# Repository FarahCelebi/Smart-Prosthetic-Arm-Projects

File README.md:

## Smart Prosthetic Arm

A six-project open hardware and firmware system for a surface EMG-controlled
prosthetic arm. The system reads muscle electrical signals from surface
electrodes, classifies hand gestures in real time, and drives a
servo-actuated prosthetic hand accordingly. Each project is a self-contained,
fully documented deliverable — schematic, PCB layout, Gerbers, and README —
designed to be fabricated and tested independently before integration.

## System Architecture

```
Surface electrodes
       │
       ▼
┌─────────────────┐
│  Project 1      │  EMG Acquisition Board
│  EMG signals    │  Dual-channel INA333 + ADS1115
│  → I²C out      │  Gain ~404×, 16-bit ADC
└────────┬────────┘
         │ I²C
         ▼
┌─────────────────┐
│  Project 2      │  Gesture Classifier Firmware
│  STM32 firmware │  Real-time EMG feature extraction
│  → gesture ID   │  + ML-based gesture classification
└────────┬────────┘
         │ I²C / UART
         ▼
┌─────────────────┐     ┌─────────────────┐
│  Project 3      │     │  Project 4      │
│  Servo Driver   │     │  BLE Module     │
│  PCA9685 PWM    │     │  nRF52840       │
│  6× servo out   │     │  Wireless telem │
└────────┬────────┘     └─────────────────┘
         │
         ▼
┌─────────────────┐
│  Project 5      │  IMU + EMG Sensor Fusion
│  ICM-42688-P    │  Accelerometer + gyroscope
│  + sensor fusion│  fused with EMG for robustness
└────────┬────────┘
         │
         ▼
┌─────────────────┐
│  Project 6      │  Full Integration Capstone
│  All subsystems │  Complete assembled arm system
│  integrated     │  End-to-end validation
└─────────────────┘
```

## Projects

| # | Project | Type | Description |
|---|---|---|---|
| 01 | [EMG Acquisition Board](./Project-1-EMG-Acquisition) | PCB | Dual-channel surface EMG acquisition board using INA333 instrumentation amplifiers and an ADS1115 16-bit ADC. Conditions raw muscle signals through a 404× gain chain with high-pass filtering and anti-alias filtering before I²C output. |
| 02 | [Gesture Classifier Firmware](./Project-2-Gesture-Classifier) | Firmware | Real-time gesture classification firmware running on the STM32F411, fusing dual-channel EMG features with ICM-42688-P IMU data to classify six hand gestures. Outputs servo position commands over I²C and streams telemetry to the BLE module over UART. |
| 03 | [Servo Driver Board](./Project-3-Servo-Driver) | PCB | PCA9685-based 16-channel PWM controller driving six servo motors for prosthetic hand finger and wrist actuation over I²C. Separate 5–6V servo power rail with 2000µF bulk capacitance isolates motor switching transients from the logic supply. |
| 04 | [BLE Telemetry Module](./Project-4-BLE-Telemetry-Module) | PCB | Bare nRF52840-QIAA BLE 5.0 transceiver board with full RF front-end design including pi-network antenna matching and quarter-wave wire antenna. Accepts USB or LiPo power through a dual-input OR-ing diode circuit with a low-dropout XC6210 LDO. |
| 05 | [IMU + EMG Sensor Fusion](./Project-5-IMU+EMG-Sensor-Fusion) | PCB | ICM-42688-P 6-axis IMU board providing wrist orientation and motion data over high-speed SPI to complement EMG signals in the gesture classifier. Includes an I²C passthrough header matching the EMG board pinout for minimal wiring harness on the arm. |
| 06 | [Full Integration Capstone](./Project-6-Full-Integration-Capstone) | PCB + Firmware | Central hub board hosting the STM32F411 main MCU and routing power, I²C, SPI, and UART signals between all five subsystem boards through pinout-matched connectors. Runs the gesture classifier firmware and coordinates the complete prosthetic arm system from a single 3.7V LiPo cell. |

## Hardware Stack

| Component | Role |
|---|---|
| INA333 (×2) | Instrumentation amplifier |
| ADS1115 | 16-bit I²C ADC |
| TLV2372 | Second-stage op-amp |
| PCA9685PW | 16-channel PWM servo controller |
| nRF52840 | BLE 5.0 + ARM Cortex-M4 |
| ICM-42688-P | 6-axis IMU (accelerometer + gyroscope) |

## Tools

- KiCad (PCB design)
- GitHub Desktop (version control)
- Zephyr RTOS / STM32 HAL (firmware)

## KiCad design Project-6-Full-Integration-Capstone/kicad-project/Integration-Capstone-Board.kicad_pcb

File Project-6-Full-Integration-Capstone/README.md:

# Integration-Capstone-Board

The central hub of the Smart Prosthetic Arm system, designed as Project 6
of 6. This board hosts the main STM32F411RETx microcontroller and provides
the physical connectors, power distribution, and signal routing that ties
all five subsystem boards into a unified wearable system — the EMG
Acquisition Board, Servo Driver Board, BLE Module, IMU Sensor Fusion Board,
and the Gesture Classifier firmware running on the STM32 itself.

## Schematic

## PCB Layout

## 3D View

## Overview

Rather than designing another standalone sensor or actuator board, the
capstone solves the real system integration challenge — making five
independent boards work together reliably as a wearable prosthetic arm.
The STM32F411 reads dual-channel EMG data from the ADS1115 over I²C,
reads 6-axis IMU data from the ICM-42688-P over SPI, classifies the
fused sensor data into one of six hand gestures, sends servo position
commands to the PCA9685 over I²C, and streams telemetry to the nRF52840
BLE module over UART — all concurrently, from a single board running on
a 3.7V LiPo battery.

## System Connections

| Connector | Subsystem | Interface | Pinout match |
|---|---|---|---|
| J4 | EMG Acquisition Board | I²C1 | Matches EMG board J3 |
| J5 | IMU Sensor Fusion Board | SPI1 + INT1 | Matches IMU board J2 |
| J6 | IMU I²C Passthrough | I²C2 | Matches IMU board J3 |
| J7 | BLE Module | UART1 + SPI1 + I²C1 + SWD | Matches BLE board J3 |
| J8 | Servo Driver Board | I²C1 | Matches servo driver J9 |
| J9 | USB | Programming + CDC | Micro-B |

All connector pinouts were designed from the start of the project to match
across boards — plugging any subsystem board into its corresponding header
requires no adapter and no rewiring.

## Design Notes

**Dual I²C bus architecture:** The STM32F411 has two I²C peripherals. I²C1
(PB6/PB7) is the main system bus, shared between the EMG Acquisition Board
(ADS1115, address 0x48), the Servo Driver Board (PCA9685, address 0x40),
and the BLE module's I²C lines. I²C2 (PB10/PB11) is a dedicated bus for
the IMU board's I²C passthrough header — isolating the IMU's local I²C
traffic from the main system bus prevents address conflicts and reduces bus
loading. Separate 10kΩ pull-up pairs (R3/R4 for I²C1, R5/R6 for I²C2)
are placed immediately beside their respective connectors.

**SPI bus sharing:** SPI1 (PA5/PA6/PA7) is shared between the IMU Sensor
Fusion Board (J5) and the BLE module (J7). The IMU chip select (IMU_CS on
PA4) and the BLE module's SPI CS are managed independently by the firmware,
allowing both devices on the same SPI bus without conflict. SPI was chosen
for the IMU over I²C to allow data rates up to 24MHz — necessary for high
ODR IMU sampling concurrent with BLE activity.

**Power architecture:** A single LiPo cell (3.7V nominal) connects to J1.
The AMS1117-3.3 LDO (U1) regulates this to 3.3V for the STM32, crystal,
and all subsystem connector power pins. A 100µF bulk electrolytic capacitor
(C5) is placed immediately at J1 to handle inrush current during system
startup when all five subsystem boards power up simultaneously. J2 is a
separate screw terminal for the 6V servo power rail — this passes directly
to the Servo Driver Board via cable and is never routed across the
integration board's PCB, keeping high-current servo switching noise isolated
from the logic rail.

**Crystal and USB:** A 25MHz crystal (Y1) provides the STM32's PLL
reference for accurate USB CDC operation. Load capacitors C6 and C7 (12pF
each) are placed immediately beside PH0 and PH1 with no vias on the
oscillator traces. USB D+ and D− pass through the USBLC6-2SC6 ESD
protection device (U3) placed immediately adjacent to J9, then through 22Ω
series resistors before reaching PA11 and PA12. The USB VBUS pin connects
to the VBAT net — when USB is connected it powers the board directly,
supplementing or replacing the LiPo without additional power management
circuitry.

**Reset and boot:** SW1 is a tactile push button connected to NRST with a
10kΩ pull-up to +3.3V, placed close to U2's NRST pin to minimise the reset
trace length. R2 pulls BOOT0 low by default for normal flash execution mode.
J3 is a 2-pin BOOT0 header that allows the STM32 to be put into DFU mode
by bridging pin 1 to +3.3V — used for initial firmware flashing before the
USB CDC interface is operational.

**Status LEDs:** Three LEDs provide system state visibility. D1 (green,
always on) connects directly from +3.3V through R9 — it illuminates
whenever the board is powered, requiring no firmware. D2 (blue) is driven
by PA3 through R10 and is toggled by firmware to indicate an active BLE
connection. D3 (yellow) is driven by PB0 through R11 and pulses on each
recognised gesture event. All three resistors are 330Ω giving approximately
8mA LED current at 3.3V supply — visible in indoor and outdoor conditions
without excessive current draw from the battery.

**Stackup rationale:** F.Cu carries all signal and power traces with no
copper pour. B.Cu carries a solid unbroken GND plane across the entire
board. This gives every signal trace — including the dense I²C, SPI, and
UART routing between U2 and the subsystem connectors — a direct return path
immediately beneath it, minimising crosstalk between the parallel bus
signals. A minimum of 4 vias are placed through the STM32's exposed GND pad
to the B.Cu plane for both electrical and thermal connection. Stitching vias
connect the board edge GND connections to the B.Cu plane around the
perimeter.

## GPIO Map

| GPIO | Function | Destination |
|---|---|---|
| PA3 | LED_BLE | D2 blue LED |
| PA4 | IMU_CS | J5 pin 6 |
| PA5 | SPI1_CLK | J5 pin 5, J7 pin 7 |
| PA6 | SPI1_MISO | J5 pin 4, J7 pin 6 |
| PA7 | SPI1_MOSI | J5 pin 3, J7 pin 5 |
| PA9 | UART1_TX | J7 pin 3 |
| PA10 | UART1_RX | J7 pin 4 |
| PA11 | USB_DM | J9 D− |
| PA12 | USB_DP | J9 D+ |
| PB0 | LED_GESTURE | D3 yellow LED |
| PB6 | I2C1_SCL | J4 pin 3, J7 pin 9, J8 pin 3 |
| PB7 | I2C1_SDA | J4 pin 4, J7 pin 8, J8 pin 4 |
| PB8 | IMU_INT1 | J5 pin 7 |
| PB9 | I2C2_SDA | J6 pin 4 |
| PB10 | I2C2_SCL | J6 pin 3 |
| PH0 | OSC_IN | Y1 pin 1 |
| PH1 | OSC_OUT | Y1 pin 2 |

## Manufacturing

- 2-layer stackup: F.Cu (signal + power) / B.Cu (solid GND plane)
- 1.6mm FR4, standard 1oz copper
- Passed DRC with 0 violations, 0 unconnected nets
- Gerbers and drill files generated

## Part of

Smart Prosthetic Arm — Project 6 of 6

## Tools

- KiCad

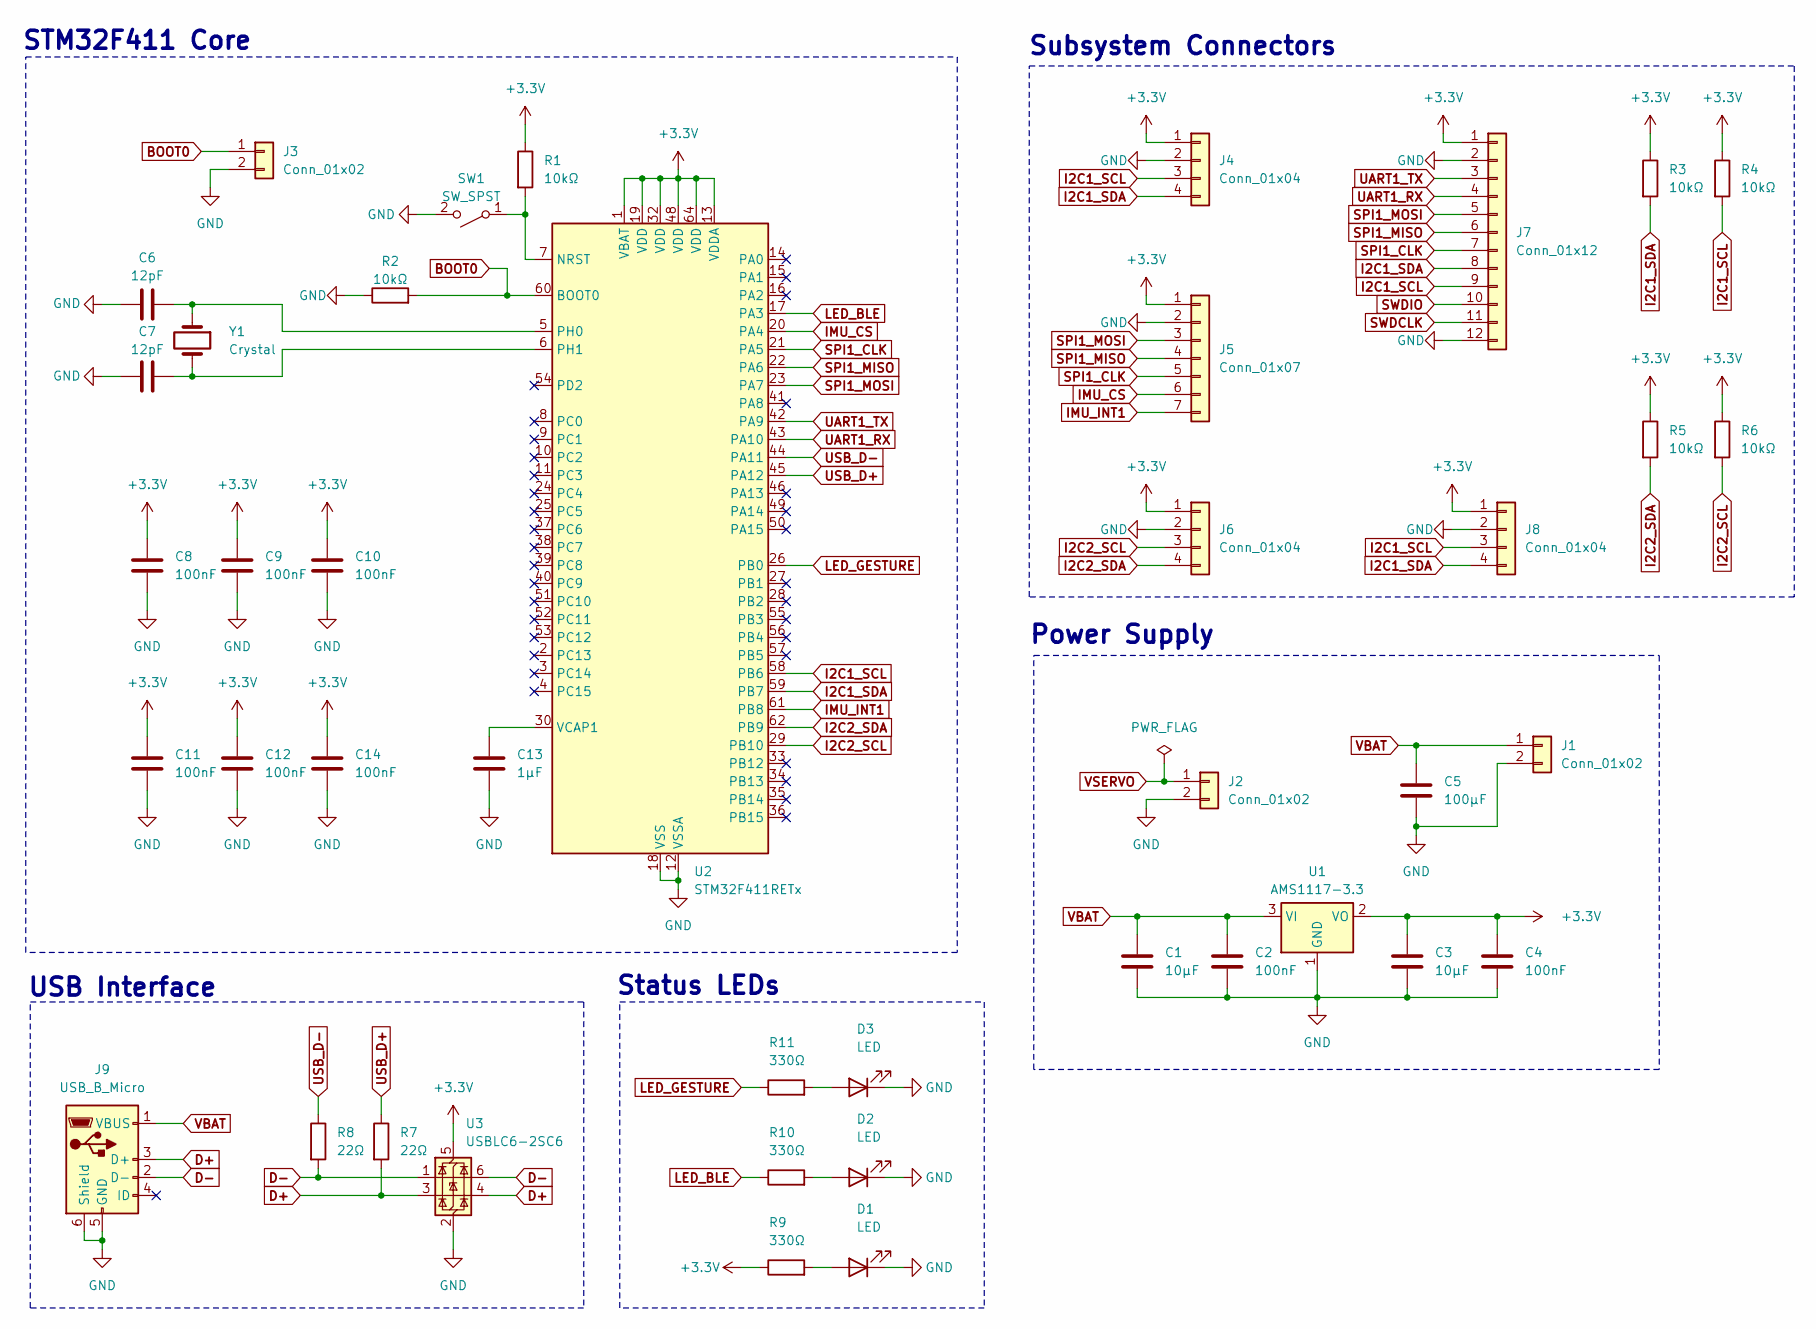
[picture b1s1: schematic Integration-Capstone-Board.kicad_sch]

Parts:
C1, C3: 10µF; C_0805_2012Metric
C2, C4, C8, C9, C10, C11, C12, C14: 100nF; C_0402_1005Metric
C5: 100µF; C_Radial_D8.0mm_H11.5mm_P3.50mm
C6, C7: 12pF; C_0402_1005Metric
C13: 1µF; C_0402_1005Metric
D1, D2, D3: LED; LED_0402_1005Metric
J1, J2: Conn_01x02; TerminalBlock_TE_282834-2_1x02_P2.54mm_Horizontal
J3: Conn_01x02; PinHeader_1x02_P2.54mm_Vertical
J4, J6, J8: Conn_01x04; PinHeader_1x04_P2.54mm_Vertical
J5: Conn_01x07; PinHeader_1x07_P2.54mm_Vertical
J7: Conn_01x12; PinHeader_1x12_P2.54mm_Vertical
J9: USB_B_Micro; USB_Micro-B_Amphenol_10118194_Horizontal
R1, R2, R3, R4, R5, R6: 10kΩ; R_0402_1005Metric
R7, R8: 22Ω; R_0402_1005Metric
R9, R10, R11: 330Ω; R_0402_1005Metric
SW1: SW_SPST; SW_SPST_PTS645Sx43SMTR92
U1: AMS1117-3.3; SOT-223-3_TabPin2
U2: STM32F411RETx; LQFP-64_10x10mm_P0.5mm
U3: USBLC6-2SC6; SOT-23-6
Y1: Crystal; Crystal_SMD_2520-4Pin_2.5x2.0mm

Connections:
+3.3V: C3.1, C4.1, C8.1, C9.1, C10.1, C11.1, C12.1, C14.1, J4.1, J5.1, J6.1, J7.1, J8.1, R1.1, R3.1, R4.1, R5.1, R6.1, R9.1, U1.2 (VO), U2.1 (VBAT), U2.13 (VDDA), U2.19 (VDD), U2.32 (VDD), U2.48 (VDD), U2.64 (VDD), U3.5 (VBUS)
BOOT0: J3.1, R2.2, U2.60 (BOOT0)
D+: J9.3 (D+), R7.2, U3.3 (I/O2), U3.4 (I/O2)
D-: J9.2 (D-), R8.2, U3.1 (I/O1), U3.6 (I/O1)
GND: C1.2, C2.2, C3.2, C4.2, C5.2, C6.1, C7.1, C8.2, C9.2, C10.2, C11.2, C12.2, C13.2, C14.2, D1.1 (K), D2.1 (K), D3.1 (K), J1.2, J2.2, J3.2, J4.2, J5.2, J6.2, J7.2, J7.12, J8.2, J9.5 (GND), J9.6 (Shield), R2.1, SW1.2 (B), U1.1 (GND), U2.12 (VSSA), U2.18 (VSS), U2.31 (VSS), U2.47 (VSS), U2.63 (VSS), U3.2 (GND), Y1.3, Y1.4
I2C1_SCL: J4.3, J7.9, J8.3, R4.2, U2.58 (PB6)
I2C1_SDA: J4.4, J7.8, J8.4, R3.2, U2.59 (PB7)
I2C2_SCL: J6.3, R6.2, U2.29 (PB10)
I2C2_SDA: J6.4, R5.2, U2.62 (PB9)
IMU_CS: J5.6, U2.20 (PA4)
IMU_INT1: J5.7, U2.61 (PB8)
LED_BLE: R10.1, U2.17 (PA3)
LED_GESTURE: R11.1, U2.26 (PB0)
unnamed: D1.2 (A), R9.2
unnamed: D2.2 (A), R10.2
unnamed: D3.2 (A), R11.2
unnamed: R1.2, SW1.1 (A), U2.7 (NRST)
unnamed: C6.2, U2.5 (PH0), Y1.1
unnamed: C7.2, U2.6 (PH1), Y1.2
unnamed: C13.1, U2.30 (VCAP1)
SPI1_CLK: J5.5, J7.7, U2.21 (PA5)
SPI1_MISO: J5.4, J7.6, U2.22 (PA6)
SPI1_MOSI: J5.3, J7.5, U2.23 (PA7)
SWDCLK: J7.11
SWDIO: J7.10
UART1_RX: J7.4, U2.43 (PA10)
UART1_TX: J7.3, U2.42 (PA9)
USB_D+: R7.1, U2.45 (PA12)
USB_D-: R8.1, U2.44 (PA11)
VBAT: C1.1, C2.1, C5.1, J1.1, J9.1 (VBUS), U1.3 (VI)
VSERVO: J2.1

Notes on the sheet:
STM32F411 Core
Status LEDs
Subsystem Connectors
Power Supply
USB Interface

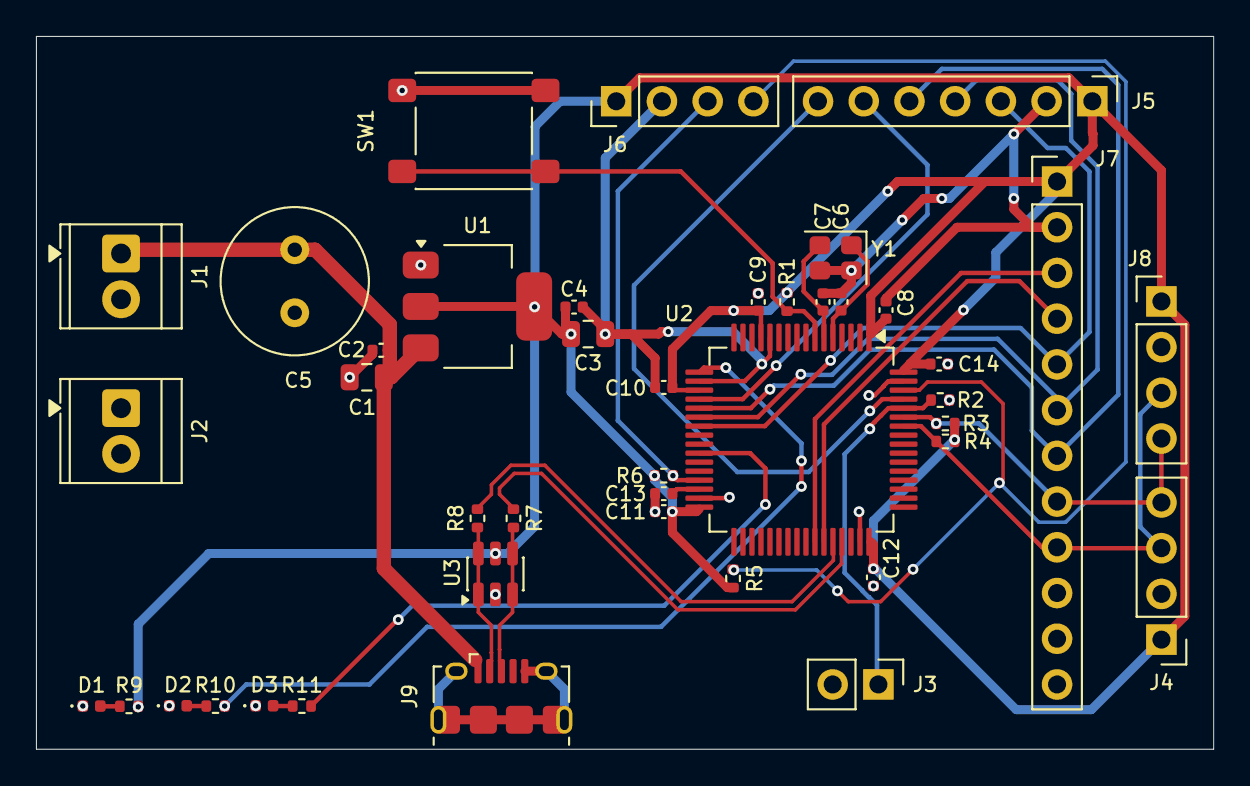
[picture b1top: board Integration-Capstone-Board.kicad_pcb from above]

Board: 2 copper layers, 65.4 x 39.6 mm, 42 parts (0 on the bottom side), 28 nets.

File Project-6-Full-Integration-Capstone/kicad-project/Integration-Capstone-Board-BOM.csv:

"Id";"Designator";"Footprint";"Quantity";"Designation";"Supplier and ref";
1;"J6,J8,J4";"PinHeader_1x04_P2.54mm_Vertical";3;"Conn_01x04";;;
2;"C3,C1";"C_0805_2012Metric";2;"10µF";;;
3;"R4,R3,R1,R5,R6,R2";"R_0402_1005Metric";6;"10kΩ";;;
4;"C5";"C_Radial_D8.0mm_H11.5mm_P3.50mm";1;"100µF";;;
5;"R10,R11,R9";"R_0402_1005Metric";3;"330Ω";;;
6;"D3,D2,D1";"LED_0402_1005Metric";3;"LED";;;
7;"U3";"SOT-23-6";1;"USBLC6-2SC6";;;
8;"C10,C12,C14,C8,C11,C4,C9,C2";"C_0402_1005Metric";8;"100nF";;;
9;"C6,C7";"C_0402_1005Metric";2;"12pF";;;
10;"C13";"C_0402_1005Metric";1;"1µF";;;
11;"U2";"LQFP-64_10x10mm_P0.5mm";1;"STM32F411RETx";;;
12;"R7,R8";"R_0402_1005Metric";2;"22Ω";;;
13;"J2,J1";"TerminalBlock_TE_282834-2_1x02_P2.54mm_Horizontal";2;"Conn_01x02";;;
14;"J3";"PinHeader_1x02_P2.54mm_Vertical";1;"Conn_01x02";;;
15;"U1";"SOT-223-3_TabPin2";1;"AMS1117-3.3";;;
16;"J7";"PinHeader_1x12_P2.54mm_Vertical";1;"Conn_01x12";;;
17;"Y1";"Crystal_SMD_2520-4Pin_2.5x2.0mm";1;"Crystal";;;
18;"J9";"USB_Micro-B_Amphenol_10118194_Horizontal";1;"USB_B_Micro";;;
19;"SW1";"SW_SPST_PTS645Sx43SMTR92";1;"SW_SPST";;;
20;"J5";"PinHeader_1x07_P2.54mm_Vertical";1;"Conn_01x07";;;

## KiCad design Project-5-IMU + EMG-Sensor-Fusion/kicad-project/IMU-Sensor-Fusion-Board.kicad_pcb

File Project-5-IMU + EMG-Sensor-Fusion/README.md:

# IMU-Sensor-Fusion-Board

A TDK InvenSense ICM-42688-P based 6-axis IMU board designed as Project 5
of the Smart Prosthetic Arm system. The board adds wrist orientation and
motion context to the dual-channel EMG signals from the EMG Acquisition
Board, enabling the gesture classifier firmware to distinguish between
gestures that produce similar EMG patterns but differ in wrist orientation —
significantly improving real-world classification accuracy.

## Schematic

## PCB Layout

## 3D View

## Overview

The ICM-42688-P integrates a 3-axis gyroscope and 3-axis accelerometer in a
compact 2.5×3.0mm LGA-14 package, providing full 6-axis motion data over a
high-speed SPI interface at up to 24MHz. The board exposes the SPI bus,
chip select, and both interrupt lines through a 7-pin header for direct
connection to the host microcontroller, and passes through the I²C bus on a
4-pin header matching the EMG Acquisition Board pinout — allowing the host
to communicate with the ADS1115 ADC and the IMU simultaneously without
additional wiring.

## Design Notes

**IMU selection:** The ICM-42688-P was selected over lower-tier IMUs such as
the MPU6050 for several reasons directly relevant to prosthetic arm use. Its
gyroscope noise density of 2.8 mdps/√Hz and accelerometer noise density of
65 µg/√Hz are among the lowest available in a single-package 6-axis device,
enabling detection of subtle wrist rotation and fine finger-positioning
gestures that would be buried in noise on a less capable sensor. The device
also supports output data rates up to 32kHz, providing substantial
oversampling headroom for the sensor fusion algorithm. The 1.71–3.6V supply
range is directly compatible with the 3.3V system rail without a dedicated
LDO.

**SPI interface:** The ICM-42688-P is operated in 4-wire SPI mode. AP_CS
(pin 12) is the chip select, held high by R1 (10kΩ pull-up to +3.3V) when
the bus is idle. AP_SCL/AP_SCLK (pin 13) is the clock, AP_SDA/AP_SDI
(pin 14) is MOSI, and AP_SDO/AP_AD0 (pin 1) is MISO. In SPI mode the
AP_AD0 function of pin 1 is overridden by the chip select state at power-up
— AP_CS tied high ensures SPI mode is selected correctly.

**Reserved pin handling:** The ICM-42688-P datasheet specifies explicit
requirements for each reserved pin. RESV_7 (pin 7) must be connected to GND
— this is mandatory and not optional. RESV_2 (pin 2) and RESV_3 (pin 3) may
be left unconnected or tied to GND — both are tied to GND on this board for
noise immunity. RESV_10 (pin 10) and RESV_11 (pin 11) may be left
unconnected — no-connect flags are placed on both.

**FSYNC/CLKIN pin (pin 9):** The INT2/FSYNC/CLKIN pin serves three functions
depending on firmware configuration. Since frame sync and external clock are
not used in this design, the pin is held low through a 10kΩ pull-down
resistor (R2) to GND. A direct GND connection was avoided because the
SnapEDA symbol defines pin 9 as bidirectional — connecting it directly to a
power symbol generates a KiCad ERC pin-type conflict. The pull-down resistor
resolves the conflict while satisfying the datasheet requirement to hold the
pin low when unused.

**Interrupt lines:** INT1 (pin 4) is broken out to pin 7 of the SPI header
as the primary data-ready interrupt — the host firmware configures INT1 to
assert when new accelerometer and gyroscope data is available in the output
registers, enabling interrupt-driven sampling without polling. INT2 is not
connected on this board — it is available for future use via firmware
reconfiguration if a second interrupt source is needed.

**Power supply and decoupling:** The board accepts 3.3V directly with no
onboard LDO. Three decoupling capacitors are placed at the power input: C1
(10µF bulk), C2 (100nF ceramic), C3 (100nF ceramic). At the ICM-42688-P
VDD pin (pin 8): C5 (100nF) and C6 (1µF) are placed as close as physically
possible to the pin. At VDDIO (pin 5): C4 (100nF) is placed immediately
adjacent. Keeping VDD and VDDIO decoupling separate and local is important
for a MEMS sensor — shared decoupling allows switching noise on the digital
IO rail to couple into the analog sensor supply, increasing noise floor on
both accelerometer and gyroscope outputs.

**I²C passthrough:** J3 is a 4-pin header (+3.3V, GND, SCL, SDA) with
pinout identical to the EMG Acquisition Board's J3 and the SDMMC Logger's
J4. Pull-up resistors R3 and R4 (10kΩ each to +3.3V) are placed immediately
beside J3. This header allows the host to reach the ADS1115 on the EMG board
over the same I²C bus without an additional cable run, keeping the wiring
harness on the prosthetic arm minimal.

**Stackup rationale:** F.Cu carries all signal and power traces with no
copper pour. B.Cu carries a solid unbroken GND plane across the entire board.
This gives every signal trace a direct return path immediately beneath it —
particularly important for the SPI clock and data lines where a fragmented
return path would increase crosstalk between channels. Stitching vias connect
the board edge GND connections to the B.Cu plane around the perimeter.

## Interface Headers

**J2 — SPI + Interrupt (Conn_01x07):**

| Pin | Signal |
|---|---|
| 1 | +3.3V |
| 2 | GND |
| 3 | SPI_MOSI |
| 4 | SPI_MISO |
| 5 | SPI_CLK |
| 6 | SPI_CS |
| 7 | INT1 |

**J3 — I²C Passthrough (Conn_01x04):**

| Pin | Signal |
|---|---|
| 1 | +3.3V |
| 2 | GND |
| 3 | SCL |
| 4 | SDA |

## Manufacturing

- 2-layer stackup: F.Cu (signal + power) / B.Cu (solid GND plane)
- 1.6mm FR4, standard 1oz copper
- Passed DRC with 0 violations, 0 unconnected nets
- Gerbers and drill files generated

## Part of

Smart Prosthetic Arm — Project 5 of 6

## Tools

- KiCad

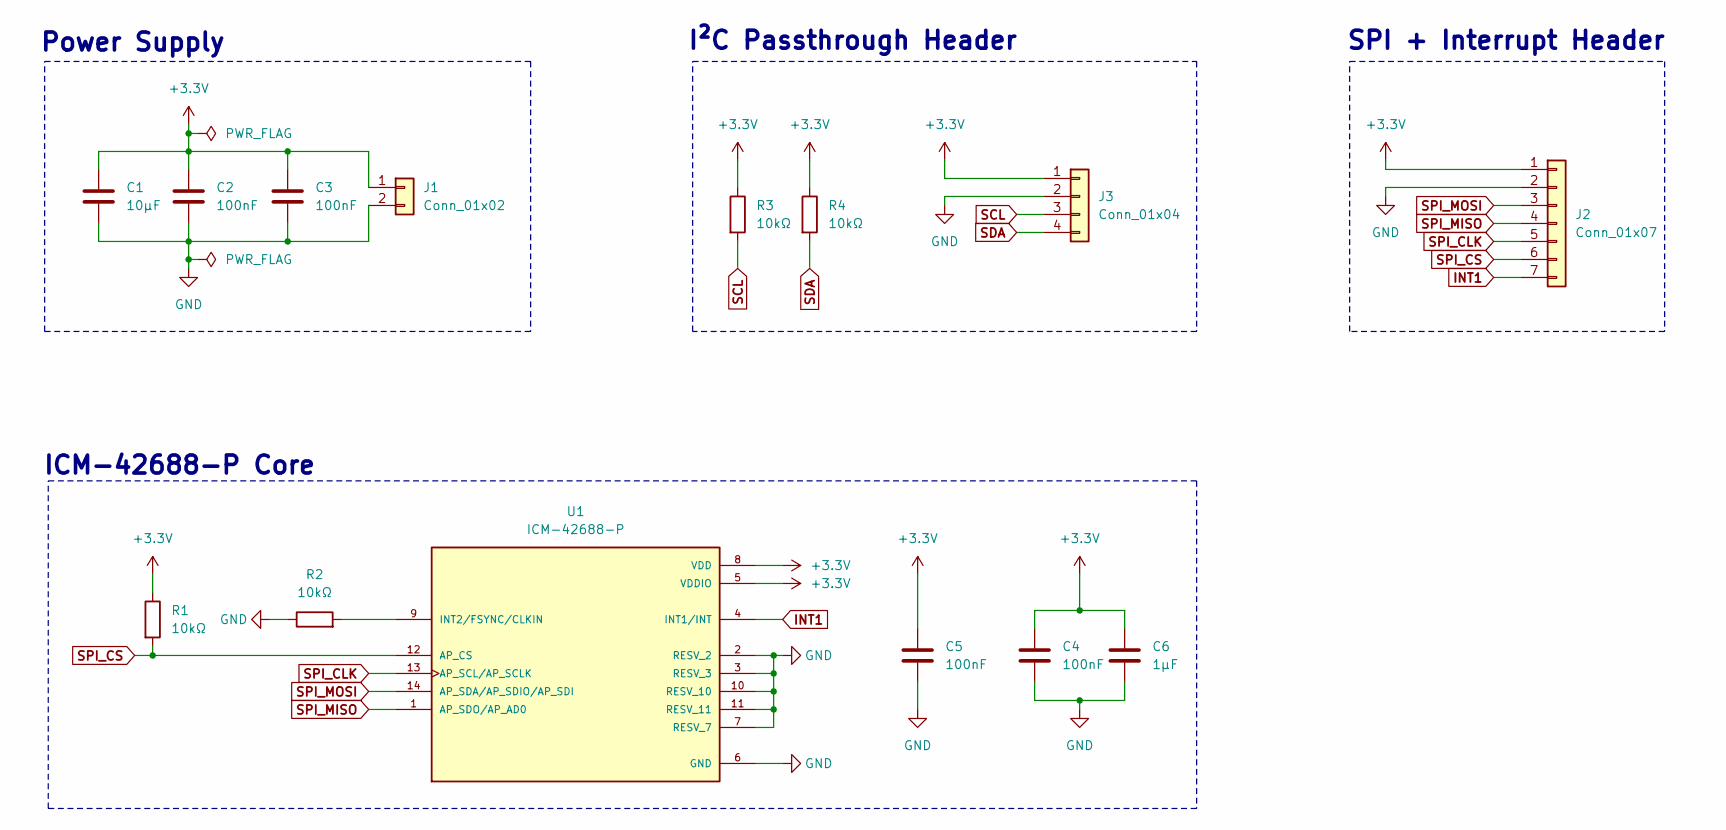
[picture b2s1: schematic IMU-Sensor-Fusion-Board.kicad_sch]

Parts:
C1: 10µF; C_0805_2012Metric
C2, C3, C4, C5: 100nF; C_0402_1005Metric
C6: 1µF; C_0402_1005Metric
J1: Conn_01x02; PinHeader_1x02_P2.54mm_Vertical
J2: Conn_01x07; PinHeader_1x07_P2.54mm_Vertical
J3: Conn_01x04; PinHeader_1x04_P2.54mm_Vertical
R1, R2, R3, R4: 10kΩ; R_0402_1005Metric
U1: ICM-42688-P; IIM42352; PARTREV 1.2

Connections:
+3.3V: C1.1, C2.1, C3.1, C4.1, C5.1, C6.1, J1.1, J2.1, J3.1, R1.1, R3.1, R4.1, U1.5 (VDDIO), U1.8 (VDD)
GND: C1.2, C2.2, C3.2, C4.2, C5.2, C6.2, J1.2, J2.2, J3.2, R2.1, U1.2 (RESV_2), U1.3 (RESV_3), U1.6 (GND), U1.7 (RESV_7), U1.10 (RESV_10), U1.11 (RESV_11)
INT1: J2.7, U1.4 (INT1/INT)
unnamed: R2.2, U1.9 (INT2/FSYNC/CLKIN)
SCL: J3.3, R3.2
SDA: J3.4, R4.2
SPI_CLK: J2.5, U1.13 (AP_SCL/AP_SCLK)
SPI_CS: J2.6, R1.2, U1.12 (AP_CS)
SPI_MISO: J2.4, U1.1 (AP_SDO/AP_AD0)
SPI_MOSI: J2.3, U1.14 (AP_SDA/AP_SDIO/AP_SDI)

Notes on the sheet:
Power Supply
I²C Passthrough Header
ICM-42688-P Core
SPI + Interrupt Header

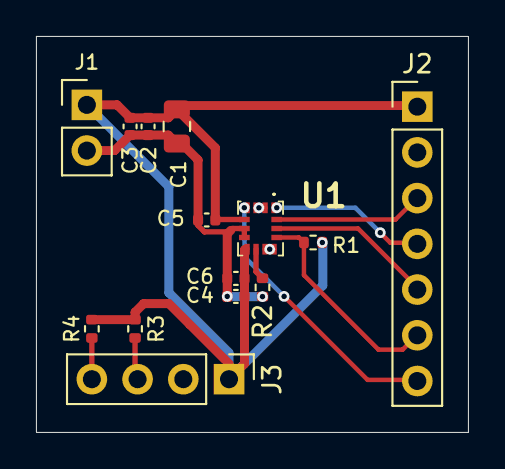
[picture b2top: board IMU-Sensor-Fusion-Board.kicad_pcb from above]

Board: 2 copper layers, 24.0 x 22.0 mm, 14 parts (0 on the bottom side), 10 nets.

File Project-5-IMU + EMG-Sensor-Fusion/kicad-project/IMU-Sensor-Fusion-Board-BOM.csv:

"Id";"Designator";"Footprint";"Quantity";"Designation";"Supplier and ref";
1;"R2,R4,R3,R1";"R_0402_1005Metric";4;"10kΩ";;;
2;"C3,C2,C4,C5";"C_0402_1005Metric";4;"100nF";;;
3;"J3";"PinHeader_1x04_P2.54mm_Vertical";1;"Conn_01x04";;;
4;"C6";"C_0402_1005Metric";1;"1µF";;;
5;"C1";"C_0805_2012Metric";1;"10µF";;;
6;"U1";"IIM42352";1;"ICM-42688-P";;;
7;"J1";"PinHeader_1x02_P2.54mm_Vertical";1;"Conn_01x02";;;
8;"J2";"PinHeader_1x07_P2.54mm_Vertical";1;"Conn_01x07";;;

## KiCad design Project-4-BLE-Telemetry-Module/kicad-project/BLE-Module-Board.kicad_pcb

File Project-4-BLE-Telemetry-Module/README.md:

# BLE-Module-Board

A Nordic nRF52840-based Bluetooth Low Energy 5.0 telemetry module designed
as Project 4 of the Smart Prosthetic Arm system. The board receives gesture
commands and EMG telemetry from the prosthetic arm system and transmits them
wirelessly to a smartphone or PC for real-time monitoring, configuration, and
data logging. It also serves as a wireless command receiver, enabling remote
arm configuration without a physical connection.

## Schematic

## PCB Layout

## 3D View

## Overview

The nRF52840 integrates a 2.4GHz BLE 5.0 radio, an ARM Cortex-M4F processor,
USB device controller, and extensive GPIO peripherals in a single aQFN-73
package. This board exposes the full interface set — UART, SPI, I²C, SWD, and
power — through a single 12-pin header, matching the pinout conventions of the
EMG Acquisition Board and SDMMC Logger for direct cable connection across the
system. A dual-input power circuit accepts either USB (5V) or a 3.7V LiPo
battery, making the board suitable for both bench development and wearable
deployment on the prosthetic arm.

## Design Notes

**Bare IC vs pre-certified module:** The nRF52840-QIAA bare IC was chosen
over a pre-certified module such as the Holyiot or u-blox NINA-B3. A module
integrates the antenna and passes regulatory certification as a unit, which
simplifies deployment but reduces design transparency and portfolio value.
Using the bare IC requires designing the RF front-end and antenna matching
network explicitly, producing a more technically rigorous board and a stronger
demonstration of RF PCB design capability.

**Power architecture — dual input OR-ing:** The board accepts power from two
sources simultaneously without conflict. USB VBUS and LiPo VBAT each feed
one anode of a BAT54S dual Schottky diode in common-cathode configuration.
The higher voltage source conducts through its diode and feeds the VSUPPLY
net; the lower voltage source is blocked automatically. VSUPPLY feeds both
the XC6210B332MR LDO (generating 3.3V for all logic) and the nRF52840's
VBUS pin (enabling the internal USB 3.3V regulator when USB is connected).
When running from LiPo only, VSUPPLY is approximately 3.4V after the diode
drop — the LDO dropout of 75mV at this level still produces a stable 3.3V
output, and the USB regulator is simply inactive. This means BLE operation
continues from battery without interruption while USB programming requires
USB connection.

**LDO selection:** The XC6210B332MR was chosen over the AMS1117-3.3 used
on previous boards specifically for its 75mV dropout voltage versus the
AMS1117's 1.3V dropout. The AMS1117 would require a minimum 4.6V input to
regulate to 3.3V — far above a LiPo battery's end-of-discharge voltage of
3.0V. The XC6210 operates reliably from VSUPPLY down to approximately 3.375V,
covering the full usable LiPo range. The CE pin is tied permanently high to
keep the regulator enabled at all times.

**RF front-end and antenna matching:** The nRF52840 ANT pin connects to a
pi-network matching circuit before the antenna connection point J_ANT. The
network consists of a 1.8pF shunt capacitor to GND on the IC side, a 3.9nH
series inductor, and a 1.5pF shunt capacitor to GND on the antenna side.
These values are taken directly from the Nordic reference schematic for a
quarter-wave wire antenna at 2.4GHz, targeting 50Ω impedance at the antenna
feed point. The entire pi-network is placed in a straight horizontal line
between the ANT pin and J_ANT, within 10mm total path length, with GND vias
immediately beside each shunt capacitor pad to minimise return-path
inductance at 2.4GHz.

**Antenna keepout zone:** A rule area covering the top-right corner of the
board prohibits copper fills on both F.Cu and B.Cu within 5mm of J_ANT and
the wire antenna. The B.Cu GND plane stops at the keepout boundary. Copper
beneath or adjacent to the antenna would detune it by acting as a parasitic
reflector, shifting the resonant frequency away from 2.4GHz and reducing
radiated efficiency. The quarter-wave wire antenna (31.25mm, λ/4 at 2.4GHz)
connects to J_ANT and extends outside the keepout zone.

**Crystal oscillators:** The nRF52840 requires two external crystals. Y1
(32MHz, 2520 SMD package, 8pF load capacitance) provides the main RF and
CPU clock reference — placed within 3mm of XC1/XC2 with no vias on the
oscillator traces. Y2 (32.768kHz, 3215 SMD package, 12.5pF load capacitance)
provides the RTC clock for low-power sleep scheduling — placed beside XL1/XL2
with vias acceptable given the low operating frequency. Load capacitors for
both crystals are placed inline between the MCU pin and the crystal pad on
the MCU side.

**DEC4 and DEC6 connection:** The Nordic datasheet requires DEC4 and DEC6
to be directly connected to each other in addition to having individual 100nF
decoupling capacitors to GND. These pins are the 1.3V internal regulator
supply decoupling nodes — the direct connection between them is mandatory per
the datasheet and is implemented with a short trace between the two pads.

**USB ESD protection:** The USBLC6-2SC6 is placed immediately adjacent to J1,
providing transient voltage suppression on both D+ and D− before the 22Ω
series resistors that connect to the nRF52840's USB pins. ESD protection must
be at the connector — placing it midway along the trace reduces its
effectiveness.

**SWD debug interface:** SWDIO and SWDCLK are exposed on pins 10 and 11 of
the 12-pin interface header J3, alongside UART, SPI, I²C, power, and GND.
A single connector handles both runtime communication and firmware programming,
eliminating the need for a separate debug header.

**Stackup rationale:** F.Cu carries all signal and power traces with no copper
pour. B.Cu carries a solid unbroken GND plane across the entire board except
the antenna keepout zone. This gives every signal trace a direct return path
immediately beneath it — the optimal configuration for a 2-layer RF board.
Stitching vias connect the board edge GND connections to the B.Cu plane every
5mm around the perimeter. A minimum of 4 vias are placed through the nRF52840
exposed die pad to the B.Cu GND plane as required for both electrical and
thermal connection.

## Interface Header Pinout (J3)

| Pin | Signal |
|---|---|
| 1 | +3.3V |
| 2 | GND |
| 3 | UART_TX |
| 4 | UART_RX |
| 5 | SPI_MOSI |
| 6 | SPI_MISO |
| 7 | SPI_CLK |
| 8 | I2C_SDA |
| 9 | I2C_SCL |
| 10 | SWDIO |
| 11 | SWDCLK |
| 12 | GND |

## Manufacturing

- 2-layer stackup: F.Cu (signal + power) / B.Cu (solid GND plane)
- 1.6mm FR4, standard 1oz copper
- Antenna keepout zone: no copper on either layer within 5mm of J_ANT
- Passed DRC with 0 violations, 0 unconnected nets
- Gerbers and drill files generated

## Part of

Smart Prosthetic Arm — Project 4 of 6

## Tools

- KiCad

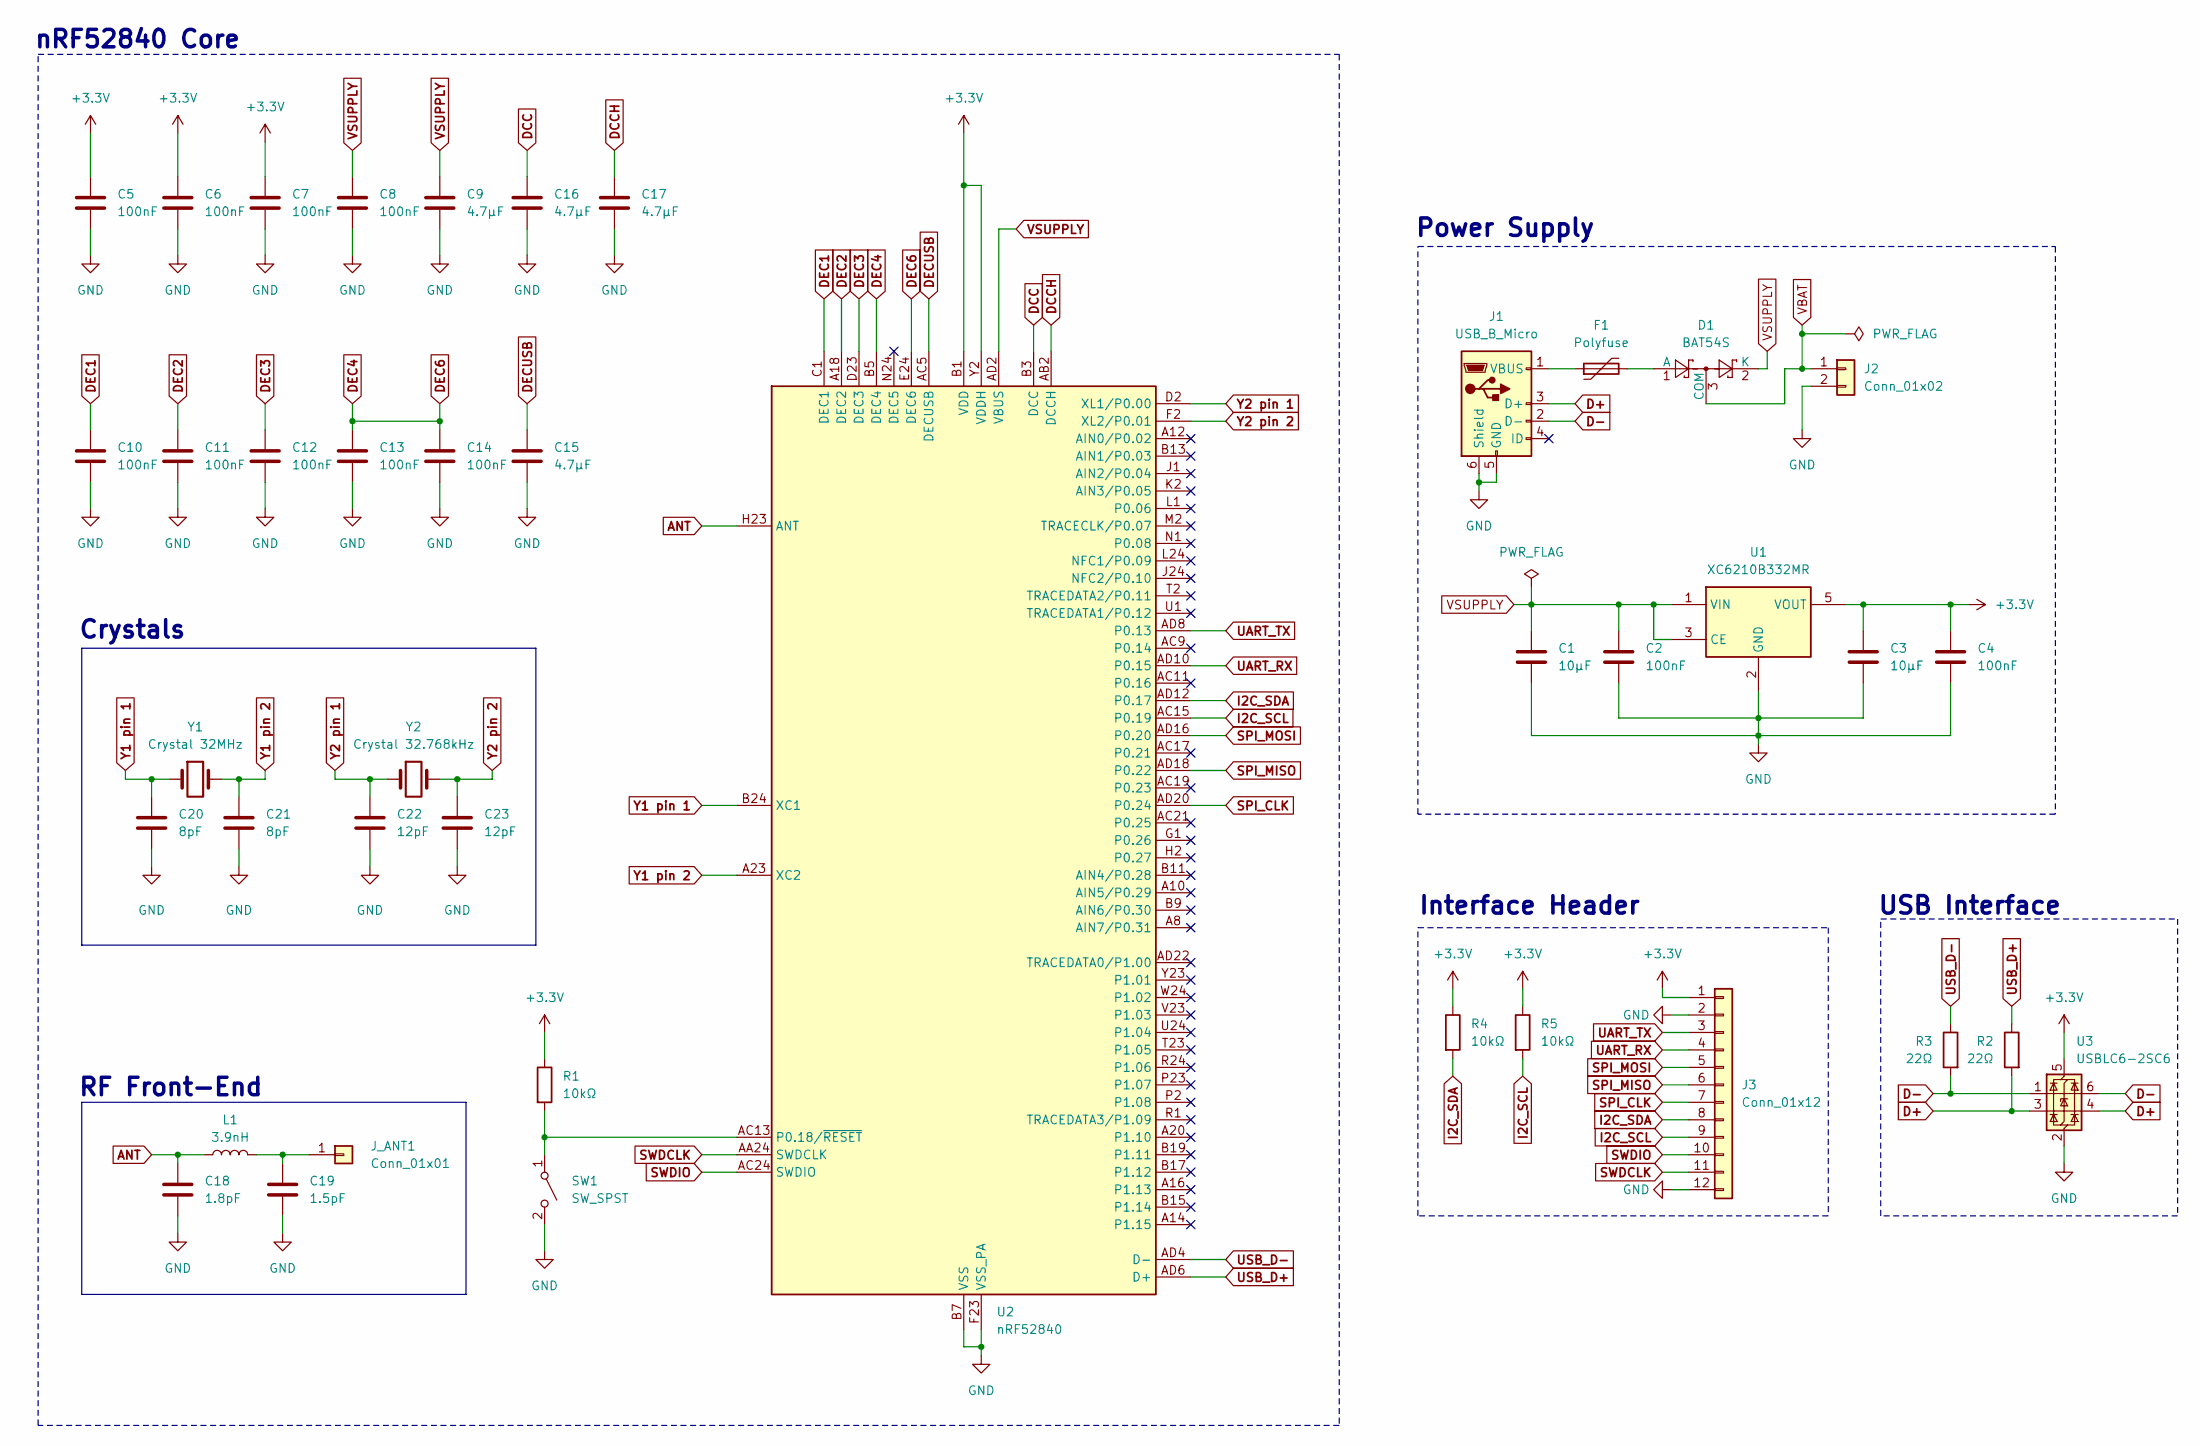
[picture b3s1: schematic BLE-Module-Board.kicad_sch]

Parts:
C1, C3: 10µF; C_0805_2012Metric
C2, C4, C5, C6, C7, C8, C10, C11, C12, C13, C14: 100nF; C_0402_1005Metric
C9, C15, C16, C17: 4.7µF; C_0805_2012Metric
C18: 1.8pF; C_0402_1005Metric
C19: 1.5pF; C_0402_1005Metric
C20, C21: 8pF; C_0402_1005Metric
C22, C23: 12pF; C_0402_1005Metric
D1: BAT54S; SOT-23
F1: Polyfuse; Fuse_1812_4532Metric
J1: USB_B_Micro; USB_Micro-B_Amphenol_10118194_Horizontal
J2: Conn_01x02; PinHeader_1x02_P2.54mm_Vertical
J3: Conn_01x12; PinHeader_1x12_P2.54mm_Vertical
J_ANT1: Conn_01x01; PinHeader_1x01_P2.54mm_Vertical
L1: 3.9nH; L_0402_1005Metric
R1, R4, R5: 10kΩ; R_0402_1005Metric
R2, R3: 22Ω; R_0402_1005Metric
SW1: SW_SPST; SW_SPST_PTS645Sx43SMTR92
U1: XC6210B332MR; SOT-23-5
U2: nRF52840; Nordic_AQFN-73-1EP_7x7mm_P0.5mm
U3: USBLC6-2SC6; SOT-23-6
Y1: Crystal 32MHz; Crystal_SMD_2520-4Pin_2.5x2.0mm
Y2: Crystal 32.768kHz; Crystal_SMD_3215-2Pin_3.2x1.5mm

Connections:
+3.3V: C3.1, C4.1, C5.1, C6.1, C7.1, J3.1, R1.1, R4.1, R5.1, U1.5 (VOUT), U2.A22 (VDD), U2.AD14 (VDD), U2.AD23 (VDD), U2.B1 (VDD), U2.W1 (VDD), U2.Y2 (VDDH), U3.5 (VBUS)
ANT: C18.1, L1.1, U2.H23 (ANT)
D+: J1.3 (D+), R2.2, U3.3 (I/O2), U3.4 (I/O2)
D-: J1.2 (D-), R3.2, U3.1 (I/O1), U3.6 (I/O1)
DCC: C16.1, U2.B3 (DCC)
DCCH: C17.1, U2.AB2 (DCCH)
DEC1: C10.1, U2.C1 (DEC1)
DEC2: C11.1, U2.A18 (DEC2)
DEC3: C12.1, U2.D23 (DEC3)
DEC4: C13.1, C14.1, U2.B5 (DEC4), U2.E24 (DEC6)
DECUSB: C15.1, U2.AC5 (DECUSB)
GND: C1.2, C2.2, C3.2, C4.2, C5.2, C6.2, C7.2, C8.2, C9.2, C10.2, C11.2, C12.2, C13.2, C14.2, C15.2, C16.2, C17.2, C18.2, C19.2, C20.2, C21.2, C22.2, C23.2, J1.5 (GND), J1.6 (Shield), J2.2, J3.2, J3.12, SW1.2 (B), U1.2 (GND), U2.B7 (VSS), U2.EP (VSS), U2.F23 (VSS_PA), U3.2 (GND), Y1.3, Y1.4
I2C_SCL: J3.9, R5.2, U2.AC15 (P0.19)
I2C_SDA: J3.8, R4.2, U2.AD12 (P0.17)
unnamed: D1.1 (A), F1.2
unnamed: F1.1, J1.1 (VBUS)
unnamed: C19.1, J_ANT1.1, L1.2
unnamed: R1.2, SW1.1 (A), U2.AC13 (P0.18/~RESET)
SPI_CLK: J3.7, U2.AD20 (P0.24)
SPI_MISO: J3.6, U2.AD18 (P0.22)
SPI_MOSI: J3.5, U2.AD16 (P0.20)
SWDCLK: J3.11, U2.AA24 (SWDCLK)
SWDIO: J3.10, U2.AC24 (SWDIO)
UART_RX: J3.4, U2.AD10 (P0.15)
UART_TX: J3.3, U2.AD8 (P0.13)
USB_D+: R2.1, U2.AD6 (D+)
USB_D-: R3.1, U2.AD4 (D-)
VBAT: D1.3 (COM), J2.1
VSUPPLY: C1.1, C2.1, C8.1, C9.1, D1.2 (K), U1.1 (VIN), U1.3 (CE), U2.AD2 (VBUS)
Y1 pin 1: C20.1, U2.B24 (XC1), Y1.1
Y1 pin 2: C21.1, U2.A23 (XC2), Y1.2
Y2 pin 1: C22.1, U2.D2 (XL1/P0.00), Y2.1
Y2 pin 2: C23.1, U2.F2 (XL2/P0.01), Y2.2

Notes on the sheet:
USB Interface
RF Front-End
Crystals
Power Supply
Interface Header
nRF52840 Core

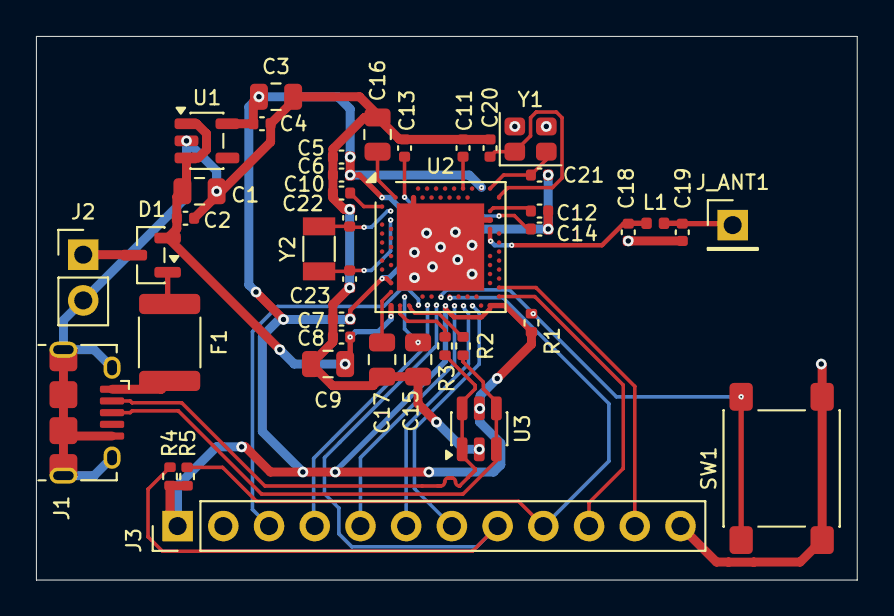
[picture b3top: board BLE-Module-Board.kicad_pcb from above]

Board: 2 copper layers, 45.6 x 30.2 mm, 41 parts (0 on the bottom side), 33 nets.

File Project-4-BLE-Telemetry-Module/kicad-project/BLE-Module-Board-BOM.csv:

"Id";"Designator";"Footprint";"Quantity";"Designation";"Supplier and ref";
1;"R2,R3";"R_0402_1005Metric";2;"22Ω";;;
2;"U2";"Nordic_AQFN-73-1EP_7x7mm_P0.5mm";1;"nRF52840";;;
3;"C18";"C_0402_1005Metric";1;"1.8pF";;;
4;"C17,C15,C16,C9";"C_0805_2012Metric";4;"4.7µF";;;
5;"C2,C8,C14,C7,C11,C12,C10,C5,C6,C13,C4";"C_0402_1005Metric";11;"100nF";;;
6;"U1";"SOT-23-5";1;"XC6210B332MR";;;
7;"C1,C3";"C_0805_2012Metric";2;"10µF";;;
8;"Y2";"Crystal_SMD_3215-2Pin_3.2x1.5mm";1;"Crystal 32.768kHz";;;
9;"F1";"Fuse_1812_4532Metric";1;"Polyfuse";;;
10;"J_ANT1";"PinHeader_1x01_P2.54mm_Vertical";1;"Conn_01x01";;;
11;"J3";"PinHeader_1x12_P2.54mm_Vertical";1;"Conn_01x12";;;
12;"C19";"C_0402_1005Metric";1;"1.5pF";;;
13;"SW1";"SW_SPST_PTS645Sx43SMTR92";1;"SW_SPST";;;
14;"C20,C21";"C_0402_1005Metric";2;"8pF";;;
15;"D1";"SOT-23";1;"BAT54S";;;
16;"C22,C23";"C_0402_1005Metric";2;"12pF";;;
17;"R4,R5,R1";"R_0402_1005Metric";3;"10kΩ";;;
18;"J2";"PinHeader_1x02_P2.54mm_Vertical";1;"Conn_01x02";;;
19;"Y1";"Crystal_SMD_2520-4Pin_2.5x2.0mm";1;"Crystal 32MHz";;;
20;"U3";"SOT-23-6";1;"USBLC6-2SC6";;;
21;"J1";"USB_Micro-B_Amphenol_10118194_Horizontal";1;"USB_B_Micro";;;
22;"L1";"L_0402_1005Metric";1;"3.9nH";;;
